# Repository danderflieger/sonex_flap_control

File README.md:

# Sonex Flap Control
This is an experimental ameteur built (EAB) electronic project that was designed for flap movement and position tracking in my Sonex B model aircraft kit. It uses an Arduino Nano in conjunction with an BTS7960/IBT_2 H-type motor driver to move the Sonex-supplied Electric Flap Actuator (Sonex part SNB-C05-11) and displays current flap position on a small OLED screen. Feel free to use it for your own purposes AT YOUR OWN RISK. It is released under MIT open source agreement license (see the license agreement listed in the root of the project). 

Multiple "notches" can be configured in software. By default, I have added 3 notches - 0 degrees, 10 degrees, and 30 degrees. Pressing the switch upward on the face triggers the arduino to retract the flaps to the previous notch. Pressing down the switch triggers the flaps to extend to the next notch. If the user presses the opposite direction, the flaps stop. However, if the pilot flips the switch in the opposite direction and holds it for more than half a second, the flaps will stop for the half second and then reverse to the next notch. The OLED screen updates constantly to notify the pilot of the current flap position. So if a builder decided to wire the switch directly to the flap actuator, the OLED screen will still keep track of the current position of the flaps, but the pilot would need to hold the switch until the flaps extend/retract to the desired position.

The code has more comment blocks than actual code describing what is happening. Pretty much every line or function has a very detailed description of what it does and what to change (if anything).

For example, after building the device it will need to be calibrated to work with your individual flap actuator (e.g. position readings are likely to be close between your flap actuator and mine, but are unlikely to be __*exactly*__ the same as mine). There is a line of code that you will want to uncomment to view the position reading on the Serial Monitor when the flaps are fully retracted and fully extended (see example below). Those values need to be entered into the code so the device can be sure to reach its __*full range*__ with your actuator. All of that is described in comment blocks in the code. Here's a sample of my comment blocks within the Arduino code file:

```
...

/**************************************************************************
These two values represent the values recevied on the A2 pin of the Arduino,
which is connected to the yellow wire of the position sensor of the flap
actuator. To calibrate your actuator, set the CALIBRATION_OUTPUT to true
and find the sensor reading that appears when  you retract/extend the flap 
actuator to its limits in both directions. Use whatever value appears in
the Serial Monitor to set the FULL_RETRACT_VALUE and FULL_EXTEND_VALUE 
settings here. Then turn off the CALIBRATION_OUTPUT by setting it to false.
No need to continue to output values to the Serial port when it's not
necessary. 
**************************************************************************/
#define FULL_RETRACT_VALUE  5
#define FULL_EXTEND_VALUE   881

/**************************************************************************
 Decide whether or not to output serial data and/or calibration data over
 the serial port (e.g. through the Arduino IDE's Serial Monitor). The 
 SERIAL_OUTPUT switch will output lots of (possibly) useful data. 
 
 If CALIBRATION_OUTPUT is set to true, it will output readings so you can 
 adjust the two values above to match the flap acutator's readings when
 it's extended/retracted fully. 
 
 It's recommended that you set the FULL_RETRACT_VALUE to 0 and the 
 FULL_EXTEND_VALUE value to 1023 to start. Then set the CALIBRATION_OUTPUT 
 value to true and retract the actuator all the way.

 The output in the Serial Monitor will tell you what to put into the 
 FULL_RETRACT_VALUE. Then extend it all the way to figure out what the 
 FULL_EXTEND_VALUE should be set to. 
**************************************************************************/
#define SERIAL_OUTPUT       false
#define CALIBRATION_OUTPUT  false

...

```

The entire code base looks similar to this, with explainations for everything that's going on. If you're not a developer, reading through the comments can help you cut your teeth on Arduino C++ coding. 

# Parts/Supplies List
Here's a list of the parts I used while prototyping. You can probably find other vendors, but your mileage will likely vary. 
### Free-standing parts
  * __Sonex Electric Flap Actuator__
The Electric Flap Actuator requires a feedback circuit. Not all Sonex Electric Flap Actuators had the feedback circuit. To verify that yours has one, you will need to look at the two sets of wires coming out of the actuator. One of them will have a red and black wire - this is for 12-24V power. The other set of wires will have three leads - blue, white, and yellow. 
  * __Arduino Nano__ (https://www.amazon.com/dp/B07G99NNXL)
  * __BTS7960/IBT_2 H-Bridge DC Motor Driver__ (https://www.amazon.com/dp/B099N8XS5P)
  * __.96 inch OLED I2C Display Module - 128x64 pixels__ (https://www.amazon.com/dp/B09T6SJBV5)
  * __Marine-grade heavy duty 12V ON-OFF-ON momentary toggle switch__ (https://www.amazon.com/dp/B0F9P9L9G6)

### PCB-related Parts
Custom Printed Cirtuit Boards are required for this project. For the prototype, I used my ancient Canon laser printer to print a mirrored image on special paper, an iron to transfer the toner to a blank single-sided 
  * __FR-4 Copper Clad PCB Laminate, Single Side, 4x2.7 inch__ (https://www.amazon.com/dp/B01MCVLDDZ)
  * __Voltage Reducer/Buck Converter (set to 9V output)__ (https://www.amazon.com/dp/B08JZ5FVLC)
  * __PCB Screw Terminal Blocks__ (https://www.amazon.com/dp/B014GMRBH2) 
  * __Straight AND Right Angle 2.54mm Male Header Pins__ (https://www.amazon.com/dp/B0CN14TP2T)
  * __2x4 8P 2.54mm Straight Male Shrouded PCB Box Header IDC Socket__ (https://www.amazon.com/dp/B08DYFQKB1)

The Socket makes connecting the custom PCB to the motor driver board very simple and clean. You have two choices for the cable - you can buy the components and make your own custom cable (which is what I did) or you can purchase one already complete. I opted to make my own because the pre-made ones are a little too long and I didn't like that. 
  * __(pre-made) 2x4 Ribbon Cable__ (https://www.amazon.com/dp/B07DFBPZLJ)
  * __(custom) 2x4 FC-8P 2.54mm Dual Rows IDC Sockets Female Connector for Flat Ribbon Cable__ (https://www.amazon.com/dp/B0BVHMTY5S)
  * __(custom) Flat Ribbon Cable for 2.54mm 0.1" Spacing Connectors__ (https://www.amazon.com/dp/B0762ZCRYN)

### Other Recommended Parts
  * __Ferrule Crimping Tool and Connectors - crimp ends of wires to reduce fatigue__ (https://www.amazon.com/dp/B0DRJ9CDNG)
  * __22 AWG Stranded Tinned Copper Wire with Silicone Insulation__ (https://www.amazon.com/dp/B0881HCN37)

# Wiring
There are two sets of wires coming out of the Electronic Flap Actuator. One set is for powering the motion of the Actuator and the other set is for reporting its position.

### Power Wires

While the actuator has a red and a black wire coming out of it for motion, they won't always be positive/negative. If you give the red wire +12V and the black wire -12V, it will extend. If you reverse the polarity (+12V to black and -12V to red) the actuator will retract:
  * 🔴 RED:   Power (+ to extend, - to retract)
  * ⚫ BLACK: Power (- to extend, + to retract)

That said, there are two options for how to wire up the power to the actuator:

* You can wire the actuator to directly use 12/24V with a 6-pole, ON-OFF-ON momentary switch wired up like this (I got this diagram from an email sent to me by Sonex Support). This requires the pilot to press and hold the switch until the flaps reach the desired position:

* -OR- You can use the motor driver to change the polarity of the actuator for you. In this case, the motor controller is controlled by the Arduino and programmed to move the actuator in notches - so the pilot just flips and releases the switch in the direction the flaps should go for literally a few milliseconds - no need to hold it - and then goes back to flying the airplane while the flaps move to the desired position with no additional input required from the pilot.

Both of these options will work with the indicator, requiring no change to the code. The Arduino will listen for switch input, but if no pilot input is received, it just merrily skips to the position reading and diplays it on the little screen. 

#### Motor Driver Use Discussion
The motor driver has several inputs and two outputs. The two outputs are the red and black wires on the actuator. The motor driver will determine how much voltage (and which polarity - remember we need to reverse the polarity to the actuator for retraction) to push to the actuator based on the other pins. Here's a list of the other pins and what they do:

* __M-__ - Output to the Actuator (this will output positive or negative power, depending on which way the actuator should move)
* __M+__ - Other output to the Actuator (this will output negative or positive power, depending on which way the actuator should move)
* __B-__ - This is the max negative power source/ground of the airplane 
* __B+__ - This is the max positive power (e.g. +12V from the battery) that can be pushed to the actuator. The Motor Driver can handle up to 36V, but I suggest just using the common 12V or 24V.
* __VCC__ - This is 5V provided by the Arduino. It's only used to power the LOGIC of the motor driver (not the motor itself)
* __GND__ - This is a common ground between the Arduino and the Motor Driver
* __R_IS__ and __L_IS__ - These two pins are not used in this project - I think they're for re-programming the motor driver or something like that. Just ignore them.
* __R_EN__ and __L_EN__ - These two pins are given 5V, which "enables" the two BTS7960 chips (one is on the right and one is on the left). If these pins are not "enabled" with 5V, the motor driver won't send any power to the Actuator
* __RPWM__ and __LPWM__ - These two pins are controlled by the Arduino - one for each BTS7960 chip on the Motor Driver board. Depending on the PWM signal from the arduino on either of these two pins, the motor driver will send a variable voltage to the actuator. To extend, we give a high PWM to the RPWM pin and NO signal to the LPWM pin. To retract, we give a high PWM signal to the LPWM pin and NO signal to the RPWM pin. see below for a description of PWM.

#### PWM Discussion
Pulse Width Modulation (PWM) is determined by turning a signal pin on and off at varying rates. Arduinos are designed to do this on their digital pins. We can set a PWM value between 0 and 255 on any Arduino digital pin. A PWM cycle is the amount of time in which a pin goes from on to off. Each PWM cycle on a typical Arduino (such as the Nano used in the project), that cycle is about every 2 milliseconds. 

A PWM value of 0 denotes that the pin is always outputting 0V. A PWM of 255 denotes that the pin
is always outputting 5V. 

A PWM output of 127 means that a pin is on (5V) for about 1ms and off (0V) for about 1ms. 

A PWM of 63 (half of 127) means that the pin will be turned on (5V) for 500 micro seconds (half of a millisecond) and off (0V) for 1500 microseconds (1.5 milliseconds). Or in other words, for about 1/4 of the cycle the pin will be outputting 5V and the other 3/4 of the cycle it will be outputting 0V.

To tell the Motor Driver to move the actuator in one direction or the other, you need to send two PWM signals - one to each of the BTS7960 chips. 

To extend the actuator, we would send a PWM of 0 to the RPWM pin and a PWM of 255 to the LPWM pin on the motor driver. This will cause the output terminal to push +12V to the red wire and -12V to the black wire on the actuator. 

To retract the actuator, we do the opposite. E.g. send a PWM of 0 to the LPWM pin and a PWM of 255 to the RPWM pin on the driver. This will revers the polarity to the actuator +12V on the BLACK wire and -12V on the RED wire. 

To slow down the motion of actuator, you would set your PWM signal at a low number - say 10. 

To speed up the movement of the actuator, you would increase the PWM to something higher - 1 to 255. 

There's a good write-up on Arduino's website about PWM - it's worth reading:
https://docs.arduino.cc/learn/microcontrollers/analog-output/ 

Note: For this project, there's no danger in just telling the motor controller to move in one direction at full speed until it reaches it's desired flap position. The actuator moves slowly enough to not worry about overshooting your flap setting by very much - I've added an additional threshold variable to account for the actuator "coasting" momentarily after telling it to stop. If set properly, this threshold will stop the actuator exactly where you want it to stop.

Now, on to the other set of wires coming out of the Electronic Flap Actuator ...

### Position Sensor Wires

The real benefit to this project is the flap position indicator. You can use the built-in position sensor to display the position of the flaps on your panel.

  * 🔵 BLUE: +5V
  * ⚪ WHITE: -5V/Ground
  * 🟡 YELLOW: 0 to +5V Signal wire (read by analog pin A2 on Arduino)

Every time the Arduino loops through the aptly named loop() function, it checks to see if there's any input from the pilot (if so, it tries to do what the pilot told it to do) and it also takes a reading from the sensor wires and updates the OLED screen with the new reading. This happens hundreds of times per second and gives near instant updates on the little screen. 

#### How the position sensor works
The position sensor is fed +5V on the blue wire and -5V on the white wire. There's a potentiometer in between with an output (yellow wire) that will output anywhere from 0V (if fully retracted) to +5V (if fully extended). If it's roughly halfway between the two, the yellow wire will output about +2.5V. 

One of the Arduino's analog pins (in this case A2) is set up to listen to the amount of voltage coming through that yellow wire. It then translates that voltage to a number between 0 and 1023. In the code, we then use a "map()" function to interpolate the value from a min/max range that the pin can read (0-1023) to a range that makes sense from a "degrees of flaps" perspective (this is defined in the code 0-30, but can be eaily changed to something else). The map() function works like this:

```
map([value recevied from yellow wire - 0-1023], [min input value - e.g. fully retracted reading], [max input value - e.g. fully extended reading], [min flap angle as defined], [max flap angle as defined]); 
```

So, given that:

* our sensor is currently sending 2.5V to the Arduino, so the Arduino reads __511__ (half way between 0 and 1023)
* our min/max values that the sensor outputs (say 0 to +5V) is converted to a number between __0__ and __1023__
* our min/max angle settings are __0__ and __30__  

that means our map() function would look like this:

__flapAngle = map(511, 0, 1023, 0, 30);__

In this case, the flapAngle variable would be set to 15 degrees of flap (e.g. half way between 0 and 30, because the actuator's sensor is reporting that it's halfway between fully extended and fully retracted). 

Once we have that value, we use a handy little OLED library written by the folks at Adafruit to draw a little rectangle on the left half of the screen (showing graphically where the flaps are currently positioned) next to a previously drawn set of lines and numbers showing where certain values will appear on the screen (on the right). 

Incedentally, we use another map() function to convert the angle value we figured out a minute ago to determine where to place the little rectangle based on the number of pixels high the screen is, minus the text at the top that says FLAPS. Giving similar values, our map() function to find the vertical position of our rectangle would look like this (where the range of available pixels is 8 to 128):

rectangleTopLeftCorner = (15, 0, 30, 8, 128); 

So the rectangleTopLeftCorner variable would be set to 60 - which means the rectangle's top left corner would be drawn on the screen at 60 pixels from the top. map() is a very handy little function!

Anyway, that's a pretty good intro. For more details, go read the comment blocks in the code - I explain a lot more there.

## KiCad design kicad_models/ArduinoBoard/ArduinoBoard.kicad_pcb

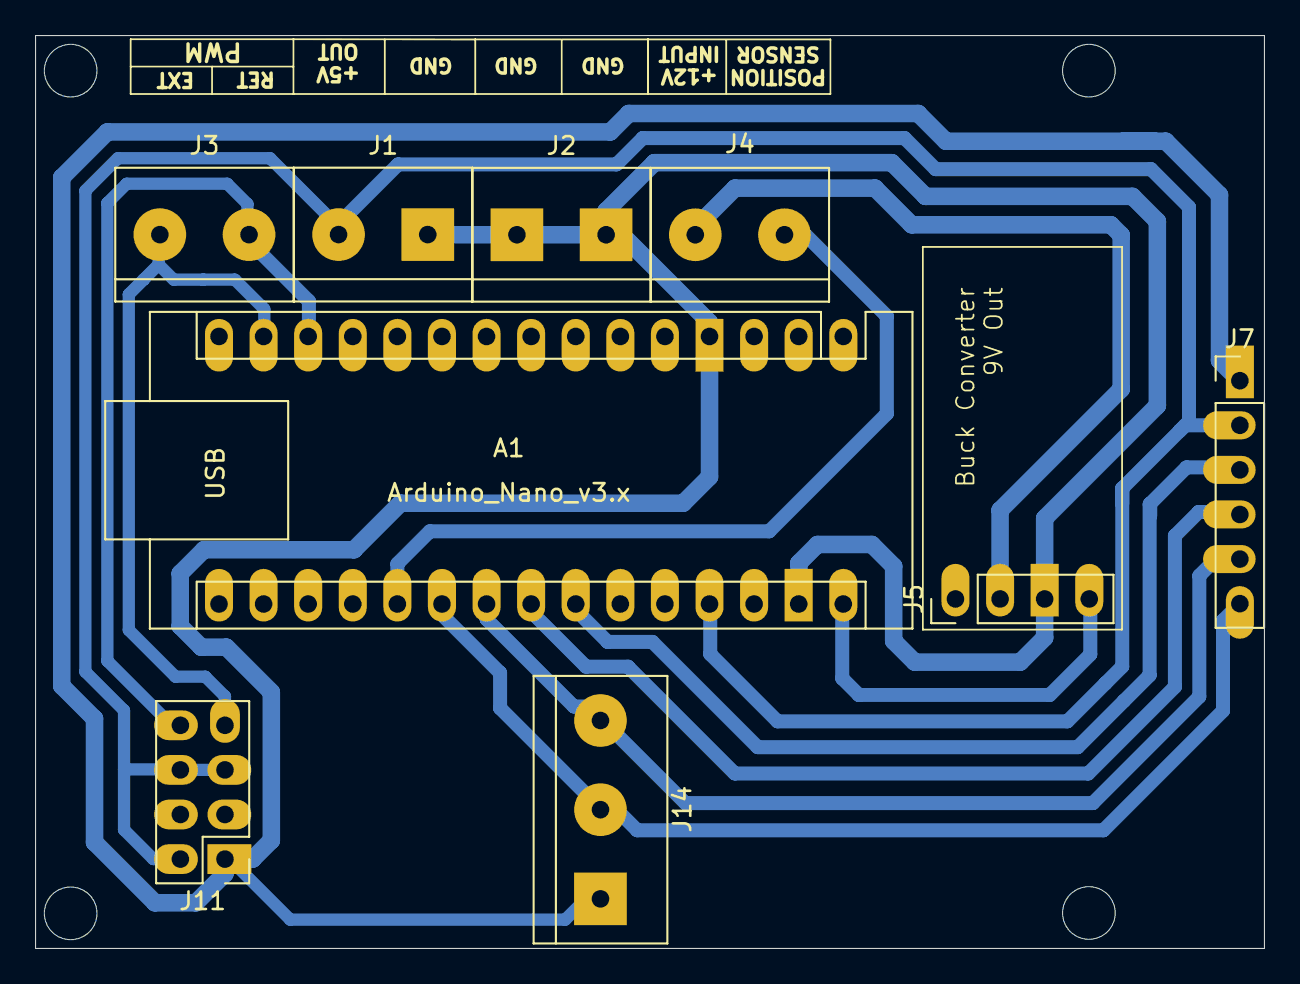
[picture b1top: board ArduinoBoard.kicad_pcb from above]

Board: 2 copper layers, 70.0 x 52.0 mm, 9 parts (0 on the bottom side), 11 nets.

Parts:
A1: Arduino_Nano_v3.x; Arduino_Nano
J1, J2: 5V Output; TerminalBlock_bornier-2_P5.08mm
J3: PWM Output; TerminalBlock_bornier-2_P5.08mm
J4: 12V Input; TerminalBlock_bornier-2_P5.08mm
J5: Conn_01x04_Pin; PinHeader_1x04_P2.54mm_Vertical
J7: Conn_01x06_Pin; PinHeader_1x06_P2.54mm_Vertical
J11: Conn_02x04_Odd_Even; PinHeader_2x04_P2.54mm_Vertical
J14: Switch/Buttons; TerminalBlock_bornier-3_P5.08mm

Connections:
/GND: A1.4 (GND), A1.29 (GND), J1.2, J2.1, J2.2, J5.3, J7.1, J11.1, J14.3
/VI+: J4.1, J5.2
/VO+: A1.30 (VIN), J5.4
unnamed: A1.27 (+5V), J1.1, J7.2, J11.2, J11.5, J11.6
unnamed: A1.20 (A1), J4.2
unnamed: A1.21 (A2), J7.6, J14.2
unnamed: A1.22 (A3), J7.5, J14.1
unnamed: A1.23 (A4), J7.4
unnamed: A1.24 (A5), J7.3
unnamed: A1.13 (D10), J3.2, J11.8
unnamed: A1.14 (D11), J3.1, J11.7

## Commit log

2025-09-05 Added .ino file to a similarly named directory (required by Arduino IDE)
2025-09-05 Added .ino to a directory.
2025-09-05 Fiddling around with placement for gauge indicator components
2025-09-06 Added actual Flap Actuator readings and code to run the motor driver. Works pretty well!
2025-09-07 Kept playing around with values. You can now add any number of "notches" with angle values (within reason - 5 notches is probably the max before pixels get overwritten). Good place to stop.
2025-09-08 Added code to extend/retract flaps by one notch when the corresponding button is pressed. This should make the workload lighter in the cockpit because you can press the button once and expect the fla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
    Untested ... fingers crossed it's correct (or close to it).
2025-09-10 Fixed a bug after testing ... still need to look at other stuff, but it's improving.
2025-09-10 Found another bug - still one more, but this is a good place to stop for now.
2025-09-10 Started adding PCB stuff.
2025-09-10 Updated the KiCad files.
2025-09-11 Updated the PCB file I was working on.
2025-09-11 Removed some old backup PCB files.
2025-09-12 Updated the kicad files some more
2025-09-13 Updated PCB file again.
2025-09-15 Had to make some updates after my first prototype PCB. Hopefully this version is correct. :)
2025-09-15 Trying to simplify code and make it match the new PCB hardware.
    Code compiles, but has some logic issues. I'm tired of looking at it
    for today.
2025-09-16 Added a 0.1uF capacitor and linked the two GND pins on the Arduino. I seem to have overloaded the Arduino when I plugged in the 12V input - probably a surge. The capacitor should condition the circui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
2025-09-16 Learned that adding a capacitor could actually make the surge worse. Changed to a Negative Temperature Coeficient (NTC) Thermistor instead. The thermistor adds resistance when cool and heats up with 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
2025-09-16 Simplified some code.
2025-09-17 Added a bunch of comment blocks to the Arduino code. Found a logic error or two that I saw as I was writing the comment blocks, so I fixed them.
2025-09-17 Made some pretty significant changes to the PCB layout. Removed the need for a via path to cross over a couple of tracks.
2025-09-18 A couple of small changes to the PCB prior to printing.
2025-09-19 Updated some code and comment blocks.
2025-09-19 Touched up the getCurrentNotch() function. It would sometimes go beyond the bounds of the ANGLES[] array and get a little funky.
    I still need to fix an issue where pressing the extend button stops at 1 degree (still in the first notch of flaps,
    but not to the second notch). It just stops. I can retract back to 0 degrees again, but it won't go farther than
    1 deg right now for some reason.
2025-09-19 Looks like I got the issue fixed. Seems to be working as expected.
2025-10-03 Started to make a 3D printable face plate with Solid Edge. Also added another child board (OLED) that allows a hole to be drilled for a 12mm momentary on-off-on switch (rather than buttons) - this up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
2025-10-04 Pushed the Arduino and other components slightly to the right to make a little more room for the switch.
2025-10-04 Updated the Solid Edge part file a little bit. Running out of time, so I'm saving my work.
2025-10-05 Added a 2x4 (8-pin) connector to the main board which allows it to connect to the motor controller with a ribbon cable.
2025-10-05 A few little updates - I was interrupted, so I can't remember what all I did. Checking in.
2025-10-12 Finished Solid Edge models (probably, anyway) including STL files. Updated some of them too. Updated the PCB board files too. I also added a boolean value called SERIAL_OUTPUT that can be switched on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
2025-10-15 Completed quit a few changes: - Arduino code is working very well. Added a TON of comment lines to describe everything that's happening - Updated the 3D models so everything fits together well and ha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
    No updates to the KiCad files - they seem to be fine.
2025-10-16 Fixed a bug where the indicator coasts a little past it's target location. Works really well now.
2025-10-21 Updated the 3D model files to fit a 2-1/4" panel cutout.
2025-10-21 Fixed an issue with the MainBoardBed.par Solid Edge file.
2025-10-21 Added a Solid Edge template for a 2-1/4" panel cutout.
2025-10-22 Added a couple of images for the Read.me file.
2025-10-24 Redesigned the PCB - moved the screw terminals for the switch to the other side of the board and changed to analog GPIO (A2 & A3) rather than Digital. Moved the two screw holes that were toward the f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
2025-10-25 A lot of changes to the 3D models to include cable management. I tried several things until I finally just settled on cutting a few oblong holes in the vertical stiffeners for cable ties. I also made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
2025-10-26 Made a few more 3D Model changes. Rotated the motor driver 90 degrees counter clockwise, which puts the wiring out the back of the device rather than off to one side. Going out the side made the wire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
2025-10-28 Hopefully a final update to the 3D models. Will put one together to see if everything fits properly.
2025-10-31 Updated the code a little, but mostly added Gerber files that can be used to purchase custom PCBs from one of the many PCB manufacturing companies.
2025-10-31 A couple of very minor code tweaks (mostly comment blocks)
2025-12-03 Updated the 3D models: - Made the MainBoardBed model a little taller and stronger (added a stringer). - Also made it possible to rotate the MotorDriverMount model upward for a shallower panel - Added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
    Exported STL files for all models.
2026-03-13 Fixed a gerber file issue reported by Jon Parnaby. He noted that a lot of the through holes in the PCBs he ordered from JLCPCB were too small (for Arduino and other components). I grew the holes from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
    Also updated the printable PDFs for PCB transfer paper (e.g. reversed, underside, copper-only).
2026-03-13 Preparing to push.
2026-04-25 Updated the MainBoardBed part to improve printability (made a flat(ish) bottom).
2026-04-25 Updated a couple of measurements on the user.1 layer.
2026-04-25 Completed changes to the MainBoardBed.par and exported to STL as well.
